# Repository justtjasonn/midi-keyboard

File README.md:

# midi-keyboard

  ** ↑↑A midi keyboard with a hexagonal theme based off of [hack club half-life's week 3 guide](https://github.com/KaiPereira/MIDI-Keypad/blob/master/README.md) ↑↑ ** 

  ## Features and components:
  - Hex shaped copper  capactive touch pads that act like keys
  - A spinning rotary encoder that controls volume
  - 2 bourns sliding potentiometers that can control expression and modulation
  - 3 customizable keys for stuff
  - designs made by me

# Design images:

| PCB | CAD/3D |
|-----------|-----------|
|  |  |
|  |  |
|  | |
|  |  |

# BOM:

**Covered by Hack Club:**

| Item | Qty | Supplier | Cost/item | Total Cost | Link |
| --- | --- | --- | --- | --- | --- |
| PCB | 1 | JLCPCB | $10.70 | $10.70 | https://jlcpcb.com/ |
| ESP-32-S3-Zero | 1 | Taobao | $3.47 | $3.47 | https://item.taobao.com/item.htm?id=964515253442 |
| Kalih low profile switches | 10 | Taobao | $0.23 | $2.30 | https://item.taobao.com/item.htm?abbucket=18&id=911127333211 |
| SK6812 LED reverse mount | 20 | Taobao | $0.04 | $0.80 | https://item.taobao.com/item.htm?id=1065391558558 |
| Alps EC11E rotary encoder switch | 1 | Taobao | $0.31 | $0.31 | https://item.taobao.com/item.htm?id=532637569029&mi_id=00000 |
| PTA2043-2010cbp103 Slide Potentiometers | 2 | Taobao | $2.40 | $4.80 | https://item.taobao.com/item.htm?id=580661983780 |
| Estimated total shipping | 1 | — | — | $9.54 | — |

**Covered by Me (Extra):**

| Item | Qty | Supplier | Cost/item | Total Cost | Link |
| --- | --- | --- | --- | --- | --- |
| 3D printed chasis | 2 | JLC3DP | $1.02 | $2.04 | https://jlc3dp.com/ |
| M3 nuts/screws | 4 | at home | $0.00 | $0.00 | my home |

# notes(Temporary):

I'll be making the firmware in week 8 is that fine i saw it in a [slack thread](https://hackclub.slack.com/archives/C0BSFN4U5E1/p1792730883112369)

# Credits:
- [Hackclub for funding and organizing everything including half life](https://hackclub.com)
- [Half life(and the organizers and helpers)](https://halflife.hackclub.com)
- [@KaiPereira for making the midi-keyboard guide](https://github.com/KaiPereira/)

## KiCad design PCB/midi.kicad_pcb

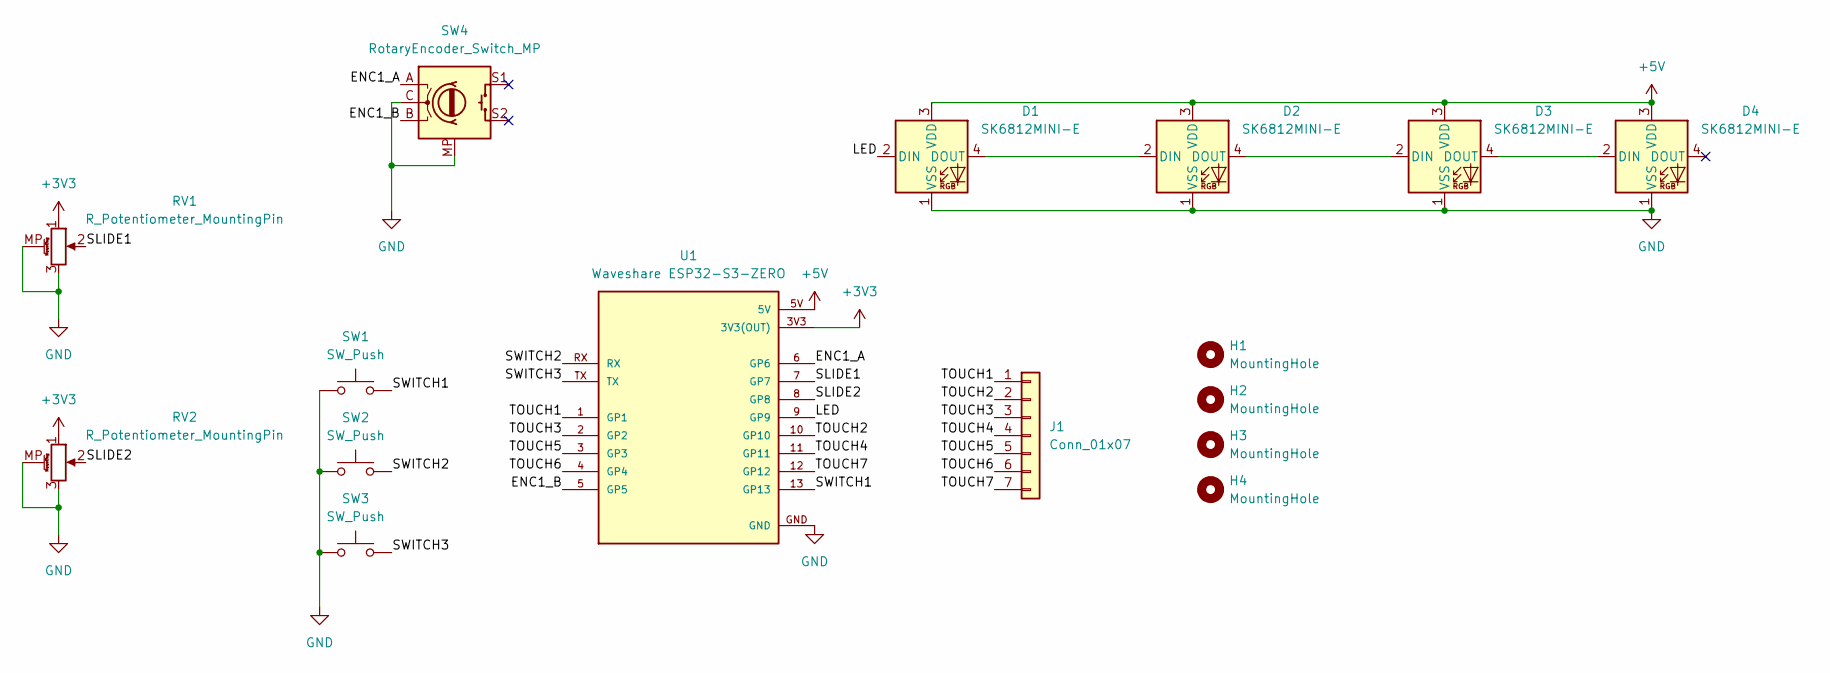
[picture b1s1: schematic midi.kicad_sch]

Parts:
D1, D2, D3, D4: SK6812MINI-E; LED_SK6812MINI-E_3.2x2.8mm_P1.5mm_ReverseMount
H1, H2, H3, H4: MountingHole; MountingHole_3.2mm_M3
J1: Conn_01x07; capactive keys
RV1, RV2: R_Potentiometer_MountingPin; Potentiometer_Bourns_PTA2043_Single_Slide
SW1, SW2, SW3: SW_Push; Kailh Choc Low-Profile Switches
SW4: RotaryEncoder_Switch_MP; RotaryEncoder_Alps_EC11E-Switch_Vertical_H20mm
U1: Waveshare ESP32-S3-ZERO; Waveshare ESP32-S3-Zero; PARTREV NA

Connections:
+3V3: RV1.1, RV2.1, U1.3V3 (3V3(OUT))
+5V: D1.3 (VDD), D2.3 (VDD), D3.3 (VDD), D4.3 (VDD), U1.5V
/ENC1_A: SW4.A, U1.6 (GP6)
/ENC1_B: SW4.B, U1.5 (GP5)
/LED: D1.2 (DIN), U1.9 (GP9)
/SLIDE1: RV1.2, U1.7 (GP7)
/SLIDE2: RV2.2, U1.8 (GP8)
/SWITCH1: SW1.2, U1.13 (GP13)
/SWITCH2: SW2.2, U1.RX
/SWITCH3: SW3.2, U1.TX
/TOUCH1: J1.1, U1.1 (GP1)
/TOUCH2: J1.2, U1.10 (GP10)
/TOUCH3: J1.3, U1.2 (GP2)
/TOUCH4: J1.4, U1.11 (GP11)
/TOUCH5: J1.5, U1.3 (GP3)
/TOUCH6: J1.6, U1.4 (GP4)
/TOUCH7: J1.7, U1.12 (GP12)
GND: D1.1 (VSS), D2.1 (VSS), D3.1 (VSS), D4.1 (VSS), RV1.3, RV1.MP (MountPin), RV2.3, RV2.MP (MountPin), SW1.1, SW2.1, SW3.1, SW4.C, SW4.MP, U1.GND
unnamed: D1.4 (DOUT), D2.2 (DIN)
unnamed: D2.4 (DOUT), D3.2 (DIN)
unnamed: D3.4 (DOUT), D4.2 (DIN)

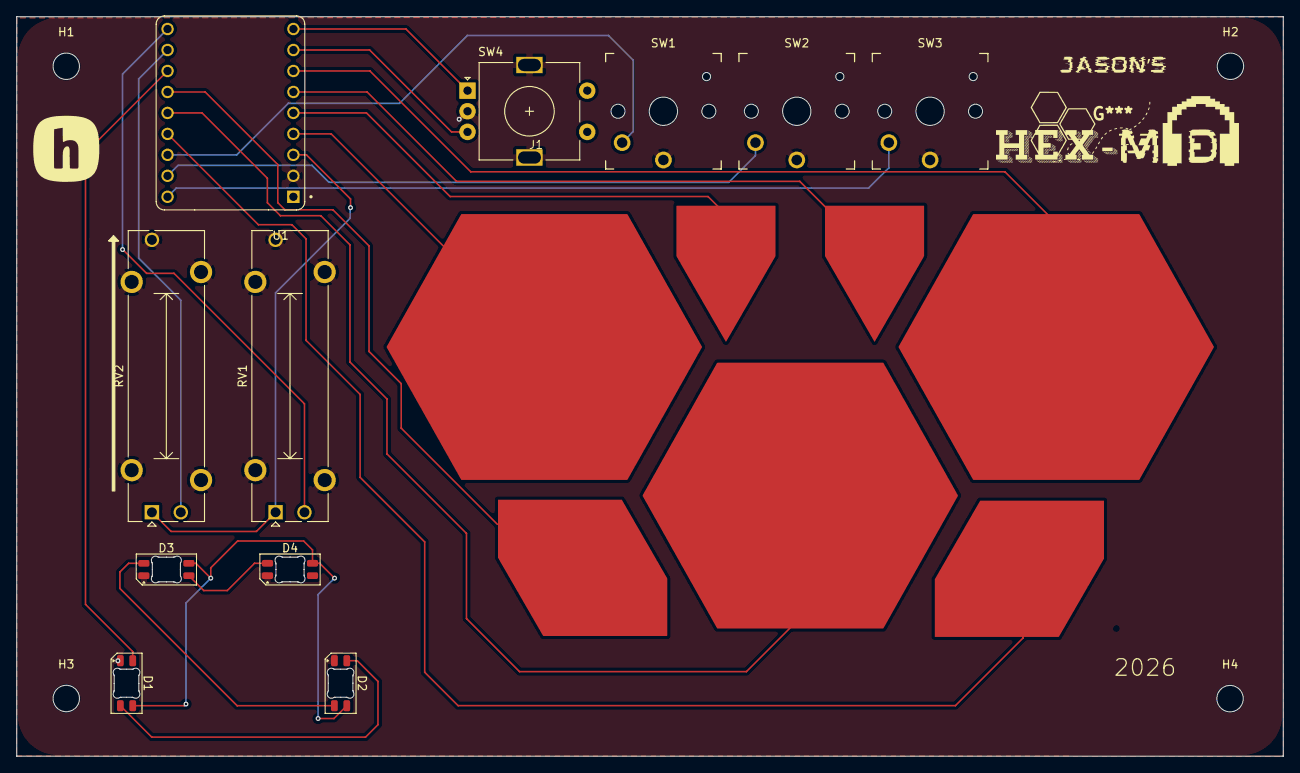
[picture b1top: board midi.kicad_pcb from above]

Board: 2 copper layers, 153.4 x 89.6 mm, 16 parts (0 on the bottom side), 21 nets.

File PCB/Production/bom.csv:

Designator,Footprint,Quantity,Value,LCSC Part #
"D1, D2, D3, D4",LED_SK6812MINI-E_3.2x2.8mm_P1.5mm_ReverseMount,4,SK6812MINI-E,
J1,capactive keys,1,Conn_01x07,
"RV1, RV2",Potentiometer_Bourns_PTA2043_Single_Slide,2,R_Potentiometer_MountingPin,
"SW1, SW2, SW3",Kailh Choc Low-Profile Switches,3,SW_Push,
SW4,RotaryEncoder_Alps_EC11E-Switch_Vertical_H20mm,1,RotaryEncoder_Switch_MP,
U1,Waveshare ESP32-S3-Zero,1,Waveshare ESP32-S3-ZERO,
